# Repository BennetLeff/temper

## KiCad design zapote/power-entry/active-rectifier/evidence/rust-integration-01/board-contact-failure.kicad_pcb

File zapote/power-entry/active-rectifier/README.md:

# Active rectifier and fused-bank construction candidate

**Development priority, 2026-09-19:** active-board construction is paused by
user direction while the [passive GBJ section](../passive-reva/MILESTONE.md)
is developed toward its protection and cooling milestone. Preserve this
experiment; resume it only after a supported net-benefit or packaging decision.

**2026-09-19 review correction:** the authored source is now an experimental
Infineon-bridge integration; `candidate/` remains the older TEA routed board.
They are deliberately different revisions, not source/PCB parity. The new
source/native construction and corrected protection logic are recorded in
[REVIEW-FIXES.md](decisions/f2-open/REVIEW-FIXES.md). Package 2 is incomplete:
no supported diode-side clamp and no complete gate-off timing budget are
established. Do not promote the new construction to routing/freeze using the
older board's reports. The following implementation description and FREEZE
apply only to the retained TEA `candidate/`.

2026-09-18. Implements the selected circuit from [CLOSEOUT](../CLOSEOUT.md).
**CAD construction checkpoint; acceptance incomplete. Do not fabricate or power
from this checkpoint.** The active Rust contract now runs against the saved board. Three TEA package
clearance findings, fuse/clip fit and Q1–Q5 qualification remain open. This is not a validated
campaign run or a protection-coordination result.

**2026-09-19 implementation:** U20 feedback now senses the diode side of F2
through authored source, compiled netlist, schematic and PCB. The
[current freeze](FREEZE.md) records fresh checks. The
[F2 transient assessment](experiments/f2-open/README.md) finds a conditional
674.7 V excursion with the existing 470 nF even with immediate switch-off;
the wiring correction does not close protection. The
[TEA reference-Gerber comparison](decisions/tea-resolution/reference-gerber/README.md)
provides no supported spacing fix. A limited
[NXP request](decisions/tea-resolution/NXP-MESSAGE.txt) is prepared and unsent.

## Implemented

- TEA2209T/1 (U1), four IPW60R017C7 (U55–U58), two 220 nF
  C0805C224K5RACTU bootstrap capacitors and 2.2 µF C0805C225K5RACTU VCC
  bypass. Four 10 Ω RC1206FR-0710RL gate-resistor tuning positions.
- Upper MOSFET drains at rectifier positive, upper sources/lower drains at
  L/R, lower sources and TEA GND on the **rectifier side** of U12. COMP_POL
  is low; COMP and HVS pins are explicitly NC. Gate disable is not mains
  disconnection. The TO-247 drain tabs are not all at the same potential:
  any shared heatsink needs an engineered electrical isolation arrangement.
- Proposed F2, Mersen A70QS50-14F, represented as U66 to preserve the source
  compiler's reference identities. `BOOST_DIODE_POSITIVE` connects U10.K,
  local U40 and U20 feedback-divider top; U66 separates that net from all four
  bulk capacitors, output and bulk bleeders. There is no copper bypass.
- Current saved feedback is **diode-side**. Opening F2 leaves the controller
  sensing the still line-fed diode-side output. The disconnected bank has no
  separate implemented voltage monitor. Remaining inductor energy, VSENSE
  filtering, controller response and no-load restart still need resolution.
  The local 470 nF remains unfused; the fused bank is nominally 2240 µF
  (~179.2 J at 400 V), not a maximum energy bound. U12/F1 still do not sense
  or interrupt the internal bank/U10/U9 loop. No shutdown credit is added.
- Preserved the passive shunt-repair board and most of its copper. This
  spacious experiment adds an 80 mm side area: **310 × 210 mm**, two layers,
  1.6 mm finished stack, 70 µm copper per side. It is not the final enclosure
  layout, a compact integration result, or a verified current-capacity design.

## Artifacts

- [Authored Atopile](../../../elec/src/power_entry_active_unit.ato).
- [PCB](candidate/section.kicad_pcb), [schematic](candidate/section.kicad_sch),
  [project](candidate/section.kicad_pro).
- [Current copper](evidence/vsense-diode-side-02/copper.svg),
  [current schematic PDF](evidence/vsense-diode-side-02/section.pdf),
  [historical pre-ECO 3D preview](evidence/rust-integration-01/board-3d.png).
  The 3D preview omits F2/clips,
  heatsinks and several inherited custom-part bodies; it cannot verify assembly fit.
- [BOM](bom.csv), [fuse mechanical review](MECHANICAL.md),
  [validation report](VALIDATION.md), [Rust integration and repairs](RUST-INTEGRATION.md),
  [replay instructions](REPRODUCE.md).

## What remains

1. Resolve three TEA footprint gaps (pads 3–5, 10–12, 14–16): 1.94 mm
   against the retained 2 mm elevated-voltage construction floor. The active
   Rust contract, NC binding, domain and current assignments now run. Routing
   repairs clear nine other spacing findings and all eight determined nominal
   branch-current findings. Surface creepage, pad/barrel capacity and active
   loss/thermal qualification remain open; see [the integration record](RUST-INTEGRATION.md).
2. Resolve the F2 clip drawing/fit and Mersen/holder application review;
   finalize the land pattern and rerun construction checks. Selected slot
   allowances and clip spacing are prototype assumptions.
3. Complete Q1–Q5: fuse coordination, surge, common mode, bootstrap/gate
   operation, startup/control behavior and installed cooling. No tests were
   run on physical hardware; no procurement or fabrication order was placed.

The native minimum-clearance DRC is not a high-voltage spacing or ampacity
qualification. Existing model/thermal results retain their original board
identities and are not rebound to this candidate.

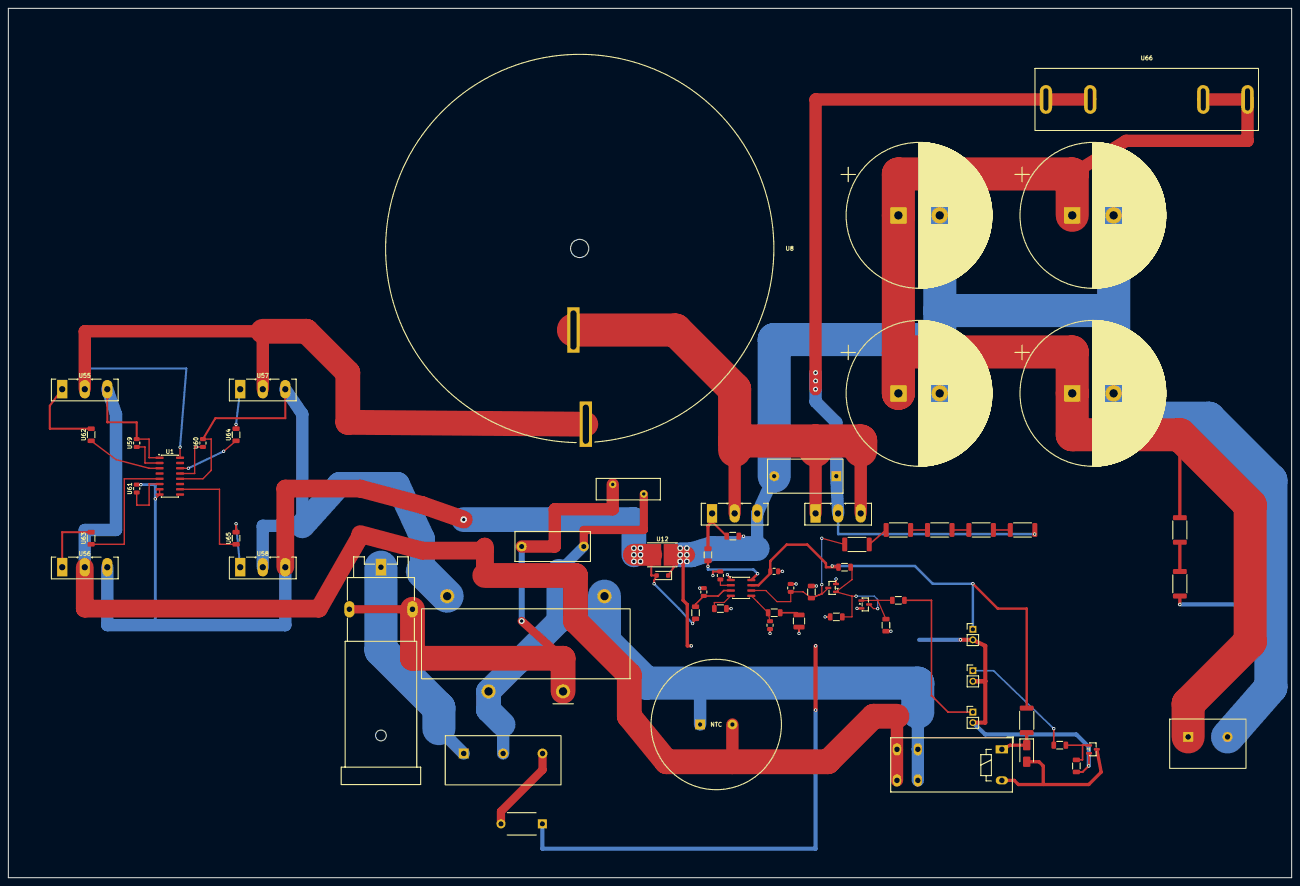
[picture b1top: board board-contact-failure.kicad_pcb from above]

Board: 2 copper layers, 310.0 x 210.0 mm, 66 parts (0 on the bottom side), 45 nets.

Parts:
U1: TEA2209T/1; SOIC-16_3.9x9.9mm_P1.27mm
U2: 0031.2510; Fuseholder_Cylinder-5x20mm_Schurter_FUP_0031.2510_Horizonta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
U3: B82726S2163N030; CMC_B82726S
U4: SL32 10015; SL32_10015
U5: RT33K012; Relay_SPST_Schrack-RT33K012
U6: 0.22uF; C_Rect_L18.0mm_W7.0mm_P15.00mm_FKS3_FKP3
U7: V150LA10AP; RV_Disc_D15.5mm_W5.2mm_P7.5mm
U8: 760800301; L_Wurth_WE-TORPFC-T75
U9: STW65N65DM2AG; TO-247-3_Vertical
U10: C3D20065D; TO-247-3_Vertical
U11: UCC28180D; SOIC-8_3.9x4.9mm_P1.27mm
U12: 10mohm; HCSM2818FT10L0
U13, U62, U63, U64, U65: 10ohm; R_1206_3216Metric
U14: 10kohm; R_1206_3216Metric
U15, U50: 1kohm; R_1206_3216Metric
U16, U48, U49, U51: 100kohm; R_1206_3216Metric
U17: 91ohm; R_2512_6332Metric
U18: 220ohm; R_1206_3216Metric
U19: 16.2kohm; R_1206_3216Metric
U20, U21, U22, U23, U24: 200kohm; R_2512_6332Metric
U25: 13kohm; R_1206_3216Metric
U26: 40.2kohm; R_1206_3216Metric
U27: 1uF; C_0805_2012Metric
U28: 2.7nF; C_0805_2012Metric
U29: 4.7uF; C_1210_3225Metric
U30, U59, U60: 220nF; C_0805_2012Metric
U31: 1nF; C_0805_2012Metric
U32: 680pF; C_0805_2012Metric
U33, U46, U47: AO3400A; SOT-23
U34: SS14; D_SMA
U35: BAT54H,115; D_SOD-123F
U36, U37, U38, U39: 560uF; CP_Radial_D35.0mm_P10.00mm_SnapIn
U40: 470nF; B32672P6474K000
U41: 1nF; C_Disc_Vishay_VY1102M31Y5UQ63V0
U42: 1714984; Phoenix_1714984
U43, U44, U45: 61300211121; PinHeader_1x02_P2.54mm_Vertical
U52: 1714971; Phoenix_1714971
U53, U54: 150kohm; R_2512_6332Metric
U55, U56, U57, U58: IPW60R017C7; TO-247-3_Vertical
U61: 2.2uF; C_0805_2012Metric
U66: A70QS50-14F; A70QS50_ETI_CH14_Prototype

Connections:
AC_L_RECTIFIED_INPUT: U2.1, U42.1
AC_N_RECTIFIED_INPUT: U3.2, U6.2, U7.2, U42.2
AUX_15V_IN: U11.7, U17.1, U27.1, U43.1, U49.1
BOOST_DIODE_POSITIVE: U10.2, U20.1, U40.1, U66.1
HOT_PERMIT_EXTERNAL: U45.1, U50.1
PE_CHASSIS: U41.2, U42.3
PFC_BUS_MINUS: U9.3, U11.1, U12.1, U14.2, U16.2, U19.2, U25.2, U27.2, U28.2, U29.2, U30.2, U31.2, U32.2, U33.2, U35.1, U36.2, U37.2, U38.2, U39.2, U40.2, U41.1, U43.2, U44.2, U45.2, U46.2, U47.2, U48.2, U51.2, U52.2, U54.2
PFC_BUS_PLUS_390V: U36.1, U37.1, U38.1, U39.1, U52.1, U53.1, U66.2
RECTIFIER_L: U1.1, U4.2, U5.3, U55.3, U56.2, U59.2
RECTIFIER_NEGATIVE: U1.7, U1.8, U12.2, U18.2, U35.2, U56.3, U58.3, U61.2
RECTIFIER_POSITIVE: U1.16, U8.1, U55.2, U57.2
RECTIFIER_R: U1.12, U3.3, U57.3, U58.2, U60.2
RELAY_BYPASS_CTRL: U15.1, U44.1
a1: U8.2, U9.2, U10.1, U10.3
bleeder1-p2: U53.2, U54.1
coil1: U5.1, U17.2, U34.1
coil2: U5.2, U33.3, U34.2
freq: U11.4, U19.1
gate: U11.8, U13.1
gatehl: U1.3, U62.1
gatehr: U1.14, U64.1
gatell: U1.5, U63.1
gatelr: U1.10, U65.1
icomp: U11.2, U28.1
isense: U11.3, U18.1, U31.1
l1: U2.2, U3.1, U6.1, U7.1
l2: U3.4, U4.1, U5.4
q_boost-g: U9.1, U13.2, U14.1
q_hl-g: U55.1, U62.2
q_hr-g: U57.1, U64.2
q_inhibit-g: U46.1, U47.3, U48.1, U49.2
q_ll-g: U56.1, U63.2
q_lr-g: U58.1, U65.2
q_permit-g: U47.1, U50.2, U51.1
r_relay_gate-g: U15.2, U16.1, U33.1
r_vcomp-p2: U26.2, U29.1
r_vtop2-p2: U21.2, U22.1
r_vtop3-p2: U22.2, U23.1
r_vtop4-p2: U23.2, U24.1
r_vtop-p2: U20.2, U21.1
vcc: U1.6, U61.1
vcchl: U1.2, U59.1
vcchr: U1.13, U60.1
vcomp: U11.5, U26.1, U30.1
vsense: U11.6, U24.2, U25.1, U32.1, U46.3

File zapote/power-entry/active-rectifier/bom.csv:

reference,source_instance,quantity,mpn,value,footprint,datasheet,role,status
U1,bridge,1,TEA2209T/1,,Package_SO:SOIC-16_3.9x9.9mm_P1.27mm,https://www.nxp.com/docs/en/data-sheet/TEA2209T.pdf,PCB component,candidate; unqualified
U2,holder,1,0031.2510,,Fuse:Fuseholder_Cylinder-5x20mm_Schurter_FUP_0031.2510_Horizontal_Closed,,PCB component,candidate; unqualified
U3,cmc,1,B82726S2163N030,,temper:CMC_B82726S,,PCB component,candidate; unqualified
U4,ntc,1,SL32 10015,,temper:SL32_10015,,PCB component,candidate; unqualified
U5,bypass,1,RT33K012,,temper:Relay_SPST_Schrack-RT33K012,,PCB component,candidate; unqualified
U6,x2,1,B32922C3224M289,0.22uF,Capacitor_THT:C_Rect_L18.0mm_W7.0mm_P15.00mm_FKS3_FKP3,,PCB component,candidate; unqualified
U7,mov,1,V150LA10AP,,Varistor:RV_Disc_D15.5mm_W5.2mm_P7.5mm,,PCB component,candidate; unqualified
U8,l_boost,1,760800301,,Inductor_THT_Wurth:L_Wurth_WE-TORPFC-T75,https://www.we-online.com/components/products/datasheet/7608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,PCB component,candidate; unqualified
U9,q_boost,1,STW65N65DM2AG,,Package_TO_SOT_THT:TO-247-3_Vertical,,PCB component,candidate; unqualified
U10,d_boost,1,C3D20065D,,Package_TO_SOT_THT:TO-247-3_Vertical,,PCB component,candidate; unqualified
U11,pfc,1,UCC28180D,,Package_SO:SOIC-8_3.9x4.9mm_P1.27mm,,PCB component,candidate; unqualified
U12,shunt,1,HCSM2818FT10L0,10mohm,temper:HCSM2818FT10L0,,PCB component,candidate; unqualified
U13,r_gate,1,RC1206FR-0710RL,10ohm,Resistor_SMD:R_1206_3216Metric,,PCB component,candidate; unqualified
U14,r_gate_pd,1,RC1206FR-0710KL,10kohm,Resistor_SMD:R_1206_3216Metric,,PCB component,candidate; unqualified
U15,r_relay_gate,1,RC1206FR-071KL,1kohm,Resistor_SMD:R_1206_3216Metric,,PCB component,candidate; unqualified
U16,r_relay_pd,1,RC1206FR-07100KL,100kohm,Resistor_SMD:R_1206_3216Metric,,PCB component,candidate; unqualified
U17,r_relay_drop,1,RC2512FR-0791RL,91ohm,Resistor_SMD:R_2512_6332Metric,,PCB component,candidate; unqualified
U18,r_isense,1,RC1206FR-07220RL,220ohm,Resistor_SMD:R_1206_3216Metric,,PCB component,candidate; unqualified
U19,r_freq,1,RC1206FR-0716K2L,16.2kohm,Resistor_SMD:R_1206_3216Metric,,PCB component,candidate; unqualified
U20,r_vtop,1,CRCW2512200KFKEG,200kohm,Resistor_SMD:R_2512_6332Metric,,PCB component,candidate; unqualified
U21,r_vtop2,1,CRCW2512200KFKEG,200kohm,Resistor_SMD:R_2512_6332Metric,,PCB component,candidate; unqualified
U22,r_vtop3,1,CRCW2512200KFKEG,200kohm,Resistor_SMD:R_2512_6332Metric,,PCB component,candidate; unqualified
U23,r_vtop4,1,CRCW2512200KFKEG,200kohm,Resistor_SMD:R_2512_6332Metric,,PCB component,candidate; unqualified
U24,r_vtop5,1,CRCW2512200KFKEG,200kohm,Resistor_SMD:R_2512_6332Metric,,PCB component,candidate; unqualified
U25,r_vbottom,1,RC1206FR-0713KL,13kohm,Resistor_SMD:R_1206_3216Metric,,PCB component,candidate; unqualified
U26,r_vcomp,1,RC1206FR-0740K2L,40.2kohm,Resistor_SMD:R_1206_3216Metric,,PCB component,candidate; unqualified
U27,c_vcc,1,C0805C105K5RACTU,1uF,Capacitor_SMD:C_0805_2012Metric,,PCB component,candidate; unqualified
U28,c_icomp,1,C0805C272J5GACTU,2.7nF,Capacitor_SMD:C_0805_2012Metric,,PCB component,candidate; unqualified
U29,c_vcomp,1,GRM32ER71H475KA88L,4.7uF,Capacitor_SMD:C_1210_3225Metric,,PCB component,candidate; unqualified
U30,c_vcomp_p,1,C0805C224K5RACTU,220nF,Capacitor_SMD:C_0805_2012Metric,,PCB component,candidate; unqualified
U31,c_isense,1,C0805C102J5GACTU,1nF,Capacitor_SMD:C_0805_2012Metric,,PCB component,candidate; unqualified
U32,c_vfeed,1,C0805C681J5GACTU,680pF,Capacitor_SMD:C_0805_2012Metric,,PCB component,candidate; unqualified
U33,relay_driver,1,AO3400A,,Package_TO_SOT_SMD:SOT-23,,PCB component,candidate; unqualified
U34,relay_flyback,1,SS14,,Diode_SMD:D_SMA,,PCB component,candidate; unqualified
U35,isense_clamp,1,"BAT54H,115",,Diode_SMD:D_SOD-123F,,PCB component,candidate; unqualified
U36,c1,1,LGX2W561MELC50,560uF,Capacitor_THT:CP_Radial_D35.0mm_P10.00mm_SnapIn,,PCB component,candidate; unqualified
U37,c2,1,LGX2W561MELC50,560uF,Capacitor_THT:CP_Radial_D35.0mm_P10.00mm_SnapIn,,PCB component,candidate; unqualified
U38,c3,1,LGX2W561MELC50,560uF,Capacitor_THT:CP_Radial_D35.0mm_P10.00mm_SnapIn,,PCB component,candidate; unqualified
U39,c4,1,LGX2W561MELC50,560uF,Capacitor_THT:CP_Radial_D35.0mm_P10.00mm_SnapIn,,PCB component,candidate; unqualified
U40,c_hf,1,B32672P6474K000,470nF,temper:B32672P6474K000,,PCB component,candidate; unqualified
U41,y1,1,VY1102M31Y5UQ63V0,1nF,Capacitor_THT:C_Disc_Vishay_VY1102M31Y5UQ63V0,,PCB component,candidate; unqualified
U42,mains,1,1714984,,temper:Phoenix_1714984,,PCB component,candidate; unqualified
U43,aux,1,61300211121,,Connector_PinHeader_2.54mm:PinHeader_1x02_P2.54mm_Vertical,,PCB component,candidate; unqualified
U44,control,1,61300211121,,Connector_PinHeader_2.54mm:PinHeader_1x02_P2.54mm_Vertical,,PCB component,candidate; unqualified
U45,permit,1,61300211121,,Connector_PinHeader_2.54mm:PinHeader_1x02_P2.54mm_Vertical,,PCB component,candidate; unqualified
U46,q_inhibit,1,AO3400A,,Package_TO_SOT_SMD:SOT-23,,PCB component,candidate; unqualified
U47,q_permit,1,AO3400A,,Package_TO_SOT_SMD:SOT-23,,PCB component,candidate; unqualified
U48,r_inhibit_pulldown,1,RC1206FR-07100KL,100kohm,Resistor_SMD:R_1206_3216Metric,,PCB component,candidate; unqualified
U49,r_inhibit_pullup,1,RC1206FR-07100KL,100kohm,Resistor_SMD:R_1206_3216Metric,,PCB component,candidate; unqualified
U50,r_permit_gate,1,RC1206FR-071KL,1kohm,Resistor_SMD:R_1206_3216Metric,,PCB component,candidate; unqualified
U51,r_permit_pd,1,RC1206FR-07100KL,100kohm,Resistor_SMD:R_1206_3216Metric,,PCB component,candidate; unqualified
U52,output,1,1714971,,temper:Phoenix_1714971,,PCB component,candidate; unqualified
U53,bleeder1,1,RC2512FR-07150KL,150kohm,Resistor_SMD:R_2512_6332Metric,,PCB component,candidate; unqualified
U54,bleeder2,1,RC2512FR-07150KL,150kohm,Resistor_SMD:R_2512_6332Metric,,PCB component,candidate; unqualified
U55,q_hl,1,IPW60R017C7,,Package_TO_SOT_THT:TO-247-3_Vertical,https://www.infineon.com/assets/row/public/documents/24/49/i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,PCB component,candidate; unqualified
U56,q_ll,1,IPW60R017C7,,Package_TO_SOT_THT:TO-247-3_Vertical,https://www.infineon.com/assets/row/public/documents/24/49/i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,PCB component,candidate; unqualified
U57,q_hr,1,IPW60R017C7,,Package_TO_SOT_THT:TO-247-3_Vertical,https://www.infineon.com/assets/row/public/documents/24/49/i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,PCB component,candidate; unqualified
U58,q_lr,1,IPW60R017C7,,Package_TO_SOT_THT:TO-247-3_Vertical,https://www.infineon.com/assets/row/public/documents/24/49/i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,PCB component,candidate; unqualified
U59,c_boot_l,1,C0805C224K5RACTU,220nF,Capacitor_SMD:C_0805_2012Metric,,PCB component,candidate; unqualified
U60,c_boot_r,1,C0805C224K5RACTU,220nF,Capacitor_SMD:C_0805_2012Metric,,PCB component,candidate; unqualified
U61,c_bridge_vcc,1,C0805C225K5RACTU,2.2uF,Capacitor_SMD:C_0805_2012Metric,,PCB component,candidate; unqualified
U62,r_hl,1,RC1206FR-0710RL,10ohm,Resistor_SMD:R_1206_3216Metric,,PCB component,candidate; unqualified
U63,r_ll,1,RC1206FR-0710RL,10ohm,Resistor_SMD:R_1206_3216Metric,,PCB component,candidate; unqualified
U64,r_hr,1,RC1206FR-0710RL,10ohm,Resistor_SMD:R_1206_3216Metric,,PCB component,candidate; unqualified
U65,r_lr,1,RC1206FR-0710RL,10ohm,Resistor_SMD:R_1206_3216Metric,,PCB component,candidate; unqualified
U66,bus_fuse,1,A70QS50-14F,,temper:A70QS50_ETI_CH14_Prototype,https://www.mersen.com/en/products/a70qs-amp-trap-form-101-s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,PCB component,candidate; unqualified
F1-link,holder insert,1,0034.3129,,installed in U2,,assembly consumable,clearing unqualified
U66-clips,bus_fuse clips,2,006710340,,included in U66 assembly footprint,https://files.eti.si/levels/en-GB/4309_TD.pdf,assembly hardware,fit and combined rating unresolved

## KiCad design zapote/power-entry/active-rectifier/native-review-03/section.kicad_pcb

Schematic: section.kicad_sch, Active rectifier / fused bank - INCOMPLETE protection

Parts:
C1, C2: 220nF; C_0805_2012Metric; MPN C0805C224K5RACTU
C3, C4: 100uF; C_Radial_D6.3mm_H11.0mm_P2.50mm; MPN EEU-FC1E101
C5, C6: 1uF; C_0603_1608Metric; MPN GRM188R71H105KA12D
C7: 4.7uF; C_0805_2012Metric; MPN GRM21BR61H475KA12L
C8: 100nF; C_0603_1608Metric; MPN C0603C104K5RACTU
C9, C10: 470pF; C_0603_1608Metric; MPN C0603C471K5RACTU
C11: 1nF; C_0603_1608Metric; MPN C0603C102K5RACTU
R1, R15: 100kohm; R_0603_1608Metric; MPN RC0603FR-07100KL
R2: 47kohm; R_0603_1608Metric; MPN RC0603FR-0747KL
R3: 150ohm; R_0603_1608Metric; MPN RC0603FR-07150RL
R4, R5: 100ohm; R_0603_1608Metric; MPN RC0603FR-07100RL
R6, R7, R8, R9: 10ohm; R_0603_1608Metric; MPN RC0603FR-0710RL
R10, R11, R12, R13, R14, R16: 10kohm; R_0603_1608Metric; MPN RC0603FR-0710KL
R17, R18: 220ohm; R_1206_3216Metric; MPN ERJ-P08J221V
U1: 0031.2510; Fuseholder_Cylinder-5x20mm_Schurter_FUP_0031.2510_Horizonta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; MPN 0031.2510
U2: B82726S2163N030; CMC_B82726S; MPN B82726S2163N030
U3: SL32 10015; SL32_10015; MPN SL32 10015
U4: RT33K012; Relay_SPST_Schrack-RT33K012; MPN RT33K012
U5: 0.22uF; C_Rect_L18.0mm_W7.0mm_P15.00mm_FKS3_FKP3; MPN B32922C3224M289
U6: V150LA10AP; RV_Disc_D15.5mm_W5.2mm_P7.5mm; MPN V150LA10AP
U7: 760800301; L_Wurth_WE-TORPFC-T75; MPN 760800301
U8: STW65N65DM2AG; TO-247-3_Vertical; MPN STW65N65DM2AG
U9: C3D20065D; TO-247-3_Vertical; MPN C3D20065D
U10: UCC28180D; SOIC-8_3.9x4.9mm_P1.27mm; MPN UCC28180D
U11: 10mohm; HCSM2818FT10L0; MPN HCSM2818FT10L0
U12: 10ohm; R_1206_3216Metric; MPN RC1206FR-0710RL
U13, U72, U78: 10kohm; R_1206_3216Metric; MPN RC1206FR-0710KL
U14, U49: 1kohm; R_1206_3216Metric; MPN RC1206FR-071KL
U15, U47, U48, U50, U76, U82, U86, U87, U89, U90: 100kohm; R_1206_3216Metric; MPN RC1206FR-07100KL
U16: 91ohm; R_2512_6332Metric; MPN RC2512FR-0791RL
U17: 220ohm; R_1206_3216Metric; MPN RC1206FR-07220RL
U18: 16.2kohm; R_1206_3216Metric; MPN RC1206FR-0716K2L
U19, U20, U21, U22, U23, U67, U68, U69, U70, U71: 200kohm; R_2512_6332Metric; MPN CRCW2512200KFKEG
U24: 13kohm; R_1206_3216Metric; MPN RC1206FR-0713KL
U25: 40.2kohm; R_1206_3216Metric; MPN RC1206FR-0740K2L
U26, U84: 1uF; C_0805_2012Metric; MPN C0805C105K5RACTU
U27: 2.7nF; C_0805_2012Metric; MPN C0805C272J5GACTU
U28: 4.7uF; C_1210_3225Metric; MPN GRM32ER71H475KA88L
U29: 220nF; C_0805_2012Metric; MPN C0805C224K5RACTU
U30: 1nF; C_0805_2012Metric; MPN C0805C102J5GACTU
U31: 680pF; C_0805_2012Metric; MPN C0805C681J5GACTU
U32, U45, U46, U85, U88: AO3400A; SOT-23; MPN AO3400A
U33: SS14; D_SMA; MPN SS14
U34: BAT54H,115; D_SOD-123F; MPN BAT54H,115
U35, U36, U37, U38: 560uF; CP_Radial_D35.0mm_P10.00mm_SnapIn; MPN LGX2W561MELC50
U39: 1.5uF; B32674D6155K000; MPN B32674D6155K000
U40: 1nF; C_Disc_Vishay_VY1102M31Y5UQ63V0; MPN VY1102M31Y5UQ63V0
U41: 1714984; Phoenix_1714984; MPN 1714984
U42, U43, U44: 61300211121; PinHeader_1x02_P2.54mm_Vertical; MPN 61300211121
U51: 1714971; Phoenix_1714971; MPN 1714971
U52, U53: 150kohm; R_2512_6332Metric; MPN RC2512FR-07150KL
U54, U55, U56, U57: IPW60R017C7; TO-247-3_Vertical; MPN IPW60R017C7
U58: A70QS50-14F; A70QS50_ETI_CH14_Prototype; MPN A70QS50-14F
U59: UCC21530BQDWKRQ1; SOIC16W_Isolated; MPN UCC21530BQDWKRQ1
U60: IR11688S; SOIC-8_3.9x4.9mm_P1.27mm; MPN IR11688S
U61, U62: BSP300H6327XUSA1; BSP300_PG-SOT223-4-21; MPN BSP300H6327XUSA1
U63: GBJ2510-F; Diode_Bridge_GBJ2510; MPN GBJ2510-F
U64: IRM-10-15; Converter_ACDC_MeanWell_IRM-10-xx_THT; MPN IRM-10-15
U65, U66: ES1J; D_SMA; MPN ES1J
U73: LM4040AIM3-5.0; SOT-23; MPN LM4040AIM3-5.0
U74: 4.7kohm; R_1206_3216Metric; MPN RC1206FR-074K7L
U75: 100nF; C_0805_2012Metric; MPN C0805C104K5RACTU
U77: 62kohm; R_1206_3216Metric; MPN RC1206FR-0762KL
U79: LM393ADR; SOIC-8_3.9x4.9mm_P1.27mm; MPN LM393ADR
U80: CD4013BM; SOIC-14_3.9x8.7mm_P1.27mm; MPN CD4013BM
U81: CD40106BM; SOIC-14_3.9x8.7mm_P1.27mm; MPN CD40106BM
U83: 300kohm; R_1206_3216Metric; MPN RC1206FR-07301KL

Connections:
AC_L_RECTIFIED_INPUT: U1.1, U41.1
AC_N_RECTIFIED_INPUT: U2.2, U5.2, U6.2, U41.2
AUX_15V: C7.1, C8.1, R2.1, R14.2, R17.1, R18.1, U10.7, U16.1, U26.1, U42.1, U48.1, U59.3, U59.8, U60.2, U61.1, U62.1, U64.4, U74.1, U76.1, U78.1, U79.8, U80.5, U80.14, U81.14, U82.1
BOOST_DIODE_POSITIVE: U9.2, U19.1, U39.1, U58.1, U67.1
BOOT_A: C1.1, C3.1, C5.1, U59.16, U65.1
BOOT_B: C2.1, C4.1, C6.1, U59.11, U66.1
CMD_A: R9.1, U59.1, U60.8
CMD_B: R8.1, U59.2, U60.1
GATE_Q1: R6.2, R10.1, U54.1
GATE_Q2: R7.2, R11.1, U56.1
GATE_Q3: R8.2, R12.1, U55.1
GATE_Q4: R9.2, R13.1, U57.1
HOT_PERMIT_EXTERNAL: U44.1, U49.1
PE_CHASSIS: U40.2, U41.3
PFC_BUS_MINUS: U8.3, U10.1, U11.1, U13.2, U15.2, U18.2, U24.2, U26.2, U27.2, U28.2, U29.2, U30.2, U31.2, U32.2, U34.1, U35.2, U36.2, U37.2, U38.2, U39.2, U40.1, U42.2, U43.2, U44.2, U45.2, U46.2, U47.2, U50.2, U51.2, U53.2, U64.3, U72.2, U73.2, U75.2, U77.2, U79.4, U80.6, U80.7, U80.8, U80.9, U80.10, U80.11, U81.7, U81.9, U81.11, U81.13, U83.2, U84.2, U85.2, U87.2, U88.2, U90.2
PFC_BUS_PLUS_390V: U35.1, U36.1, U37.1, U38.1, U51.1, U52.1, U58.2
RECTIFIER_L: C1.2, C3.2, C5.2, R10.2, U3.2, U4.3, U54.3, U55.2, U59.14, U61.2, U61.4, U63.2
RECTIFIER_NEGATIVE: C7.2, C8.2, C9.2, C10.2, C11.2, R1.2, R3.2, R12.2, R13.2, R15.2, R16.2, U11.2, U17.2, U34.2, U55.3, U57.3, U59.4, U59.7, U60.7, U63.4
RECTIFIER_POSITIVE: U7.1, U54.2, U56.2, U63.1
RECTIFIER_R: C2.2, C4.2, C6.2, R11.2, U2.3, U56.3, U57.2, U59.9, U62.2, U62.4, U63.3, U64.1
RELAY_BYPASS_CTRL: U14.1, U43.1
SENSE_A: C9.1, R4.2, U60.4
SENSE_B: C10.1, R5.2, U60.5
a1: U7.2, U8.2, U9.1, U9.3
aux_tap: U76.2, U77.1, U79.5
bleeder1-p2: U52.2, U53.1
clk1: U80.3, U81.6
coil1: U4.1, U16.2, U33.1
coil2: U4.2, U32.3, U33.2
d: U10.6, U23.2, U24.1, U31.1, U45.3, U85.3, U88.3
det_tap: U71.2, U72.1, U79.2
det_top1-p2: U67.2, U68.1
det_top2-p2: U68.2, U69.1
det_top3-p2: U69.2, U70.1
det_top4-p2: U70.2, U71.1
dt: C11.1, R16.1, U59.6
en: R14.1, R15.1, U59.5
fault_n: U78.2, U79.1, U79.7, U81.3
freq: U10.4, U18.1
gate: U10.8, U12.1
icomp: U10.2, U27.1
isense: U10.3, U17.1, U30.1
l1: U1.2, U2.1, U5.1, U6.1
l2: U2.4, U3.1, U4.4, U64.2
mot: R1.1, U60.3
nc: U73.3
outa: R6.1, U59.15
outb: R7.1, U59.10
por_node: U81.1, U82.2, U83.1, U84.1
q1: U80.1
q2: U80.13
q_boost-g: U8.1, U12.2, U13.1
q_inhibit2-g: U85.1, U86.2, U87.1
q_inhibit-g: U45.1, U46.3, U47.1, U48.2
q_permit-g: U46.1, U49.2, U50.1
q_startup-g: U88.1, U89.2, U90.1
qn1: U80.2, U86.1
qn2: U80.12
r1: U80.4, U81.4
r_boot_a-a: R17.2, U65.2
r_boot_b-a: R18.2, U66.2
r_relay_gate-g: U14.2, U15.1, U32.1
r_vcomp-p2: U25.2, U28.1
r_vtop2-p2: U20.2, U21.1
r_vtop3-p2: U21.2, U22.1
r_vtop4-p2: U22.2, U23.1
r_vtop-p2: U19.2, U20.1
ref_5v: U73.1, U74.2, U75.1, U79.3, U79.6
sense_a-s: R4.1, U61.3
sense_b-s: R5.1, U62.3
vcomp: U10.5, U25.1, U29.1
vs: R2.2, R3.1, U60.6
y1: U81.2, U81.5, U89.1
y4: U81.8
y5: U81.10
y6: U81.12

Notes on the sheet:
1800 W nominal AC input / 120 VAC / external 15 A RMS foldback required
ALL control, permit and auxiliary headers are HOT bus-minus referenced
INCOMPLETE: first-peak control / total gate-off latency OPEN. AUX produced onboard; external supervisor required.

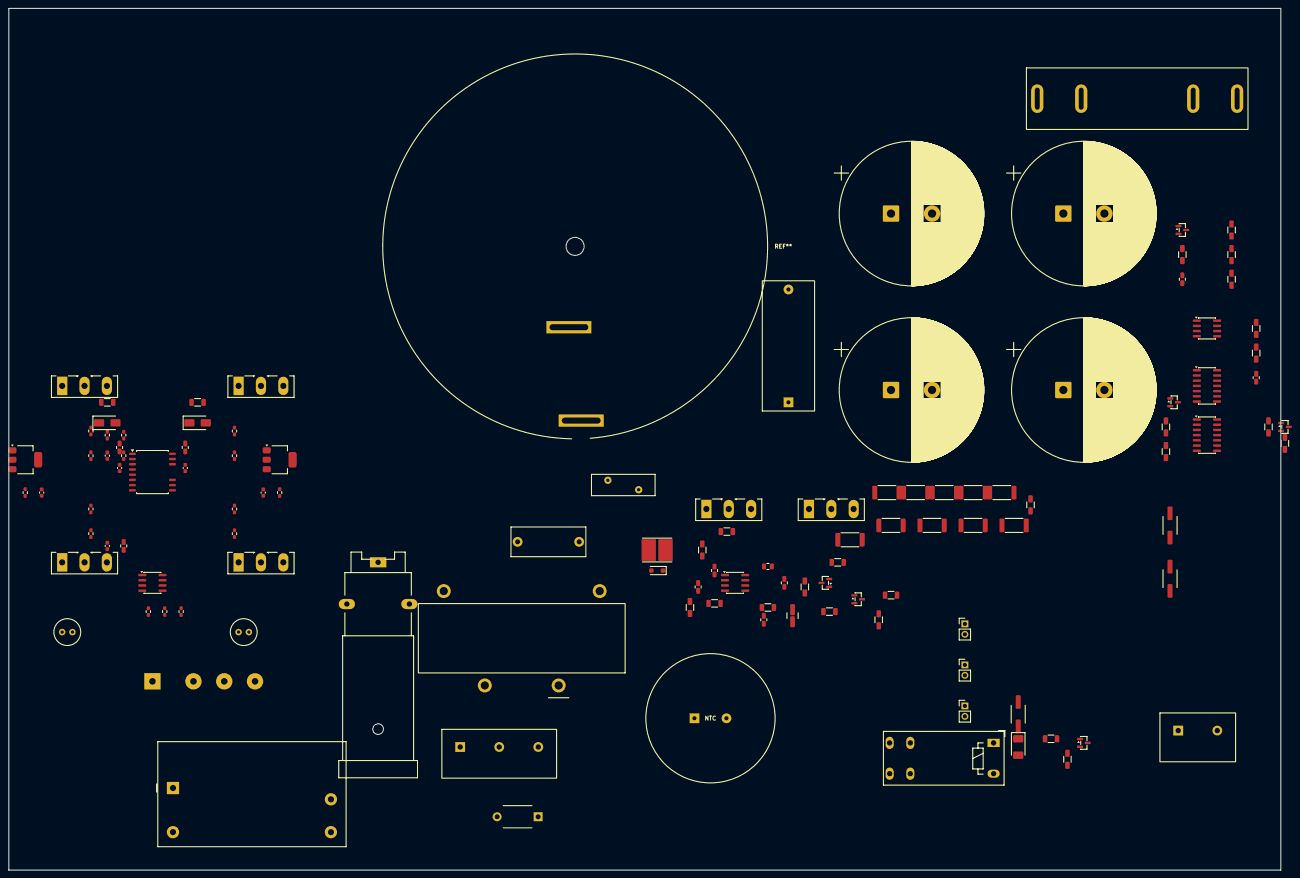
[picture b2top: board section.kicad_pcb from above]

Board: 6 copper layers, 310.0 x 210.0 mm, 119 parts (0 on the bottom side), 69 nets, no tracks yet.
